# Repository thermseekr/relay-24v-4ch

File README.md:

# RELAY-24V-4CH

Relay board with 4x 24 VDC relays. This board is designed to be used togheter with [ESP-24V-16CH](https://github.com/thermseekr/esp-24v-16ch) and [ESP-24V-32CH](https://github.com/thermseekr/esp-24v-32ch), but can be driven by any 24V control circuit compatible with NPN inputs.

The dimensions are such that the boards can be mounted on a PCB DIN rail holder from the Brazilian manufacturer Metaltex, check [here](https://www.metaltex.com.br/produtos/componentes/suportes/sp7-suporte-para-montagem-de-placa-de-circuito-impresso-em-trilho-din) for details.

Board V1 uses Omron 16A relays and is limited to 12A/channel, board V2 uses Omron 10A relays and is limited to 8A/channel. The current limits are imposed per copper trace capacity.

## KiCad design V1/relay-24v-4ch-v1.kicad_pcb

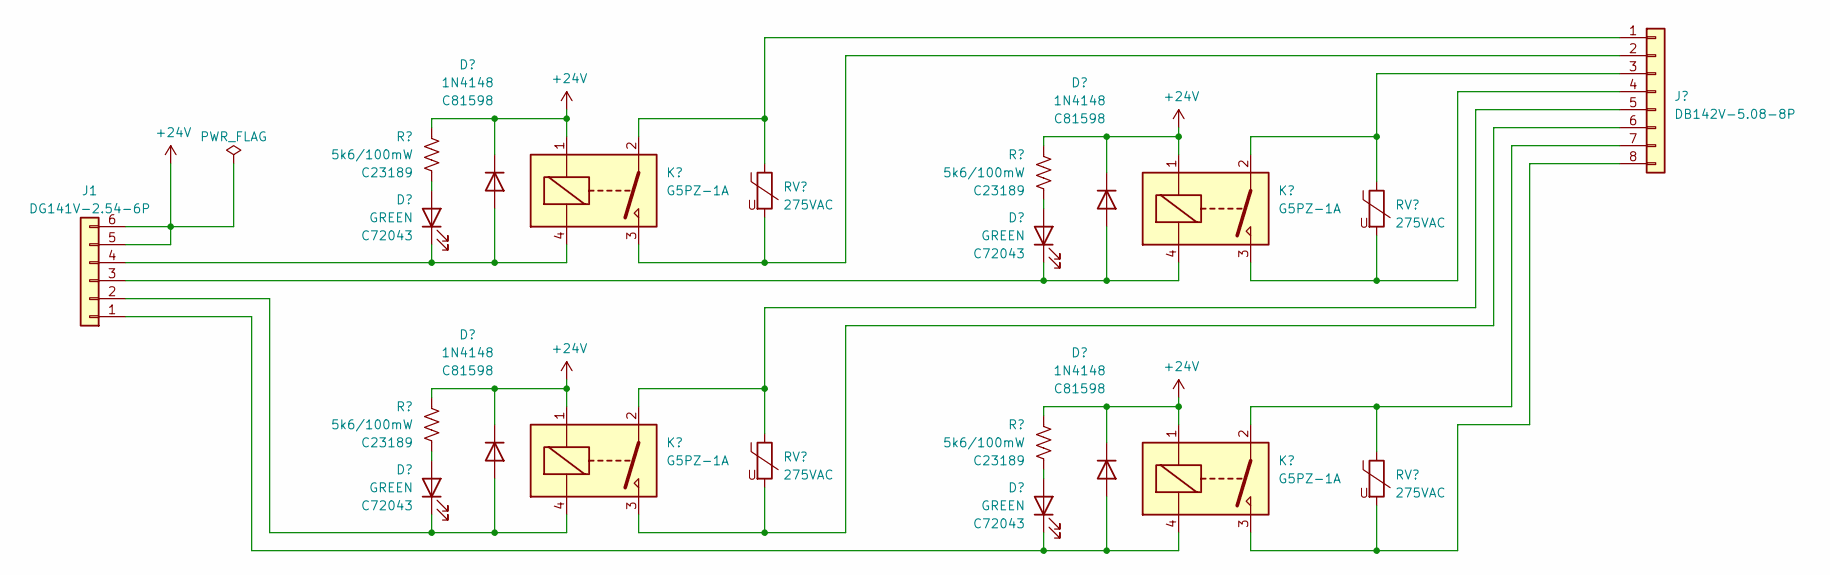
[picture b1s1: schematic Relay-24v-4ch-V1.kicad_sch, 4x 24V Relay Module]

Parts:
D1, D3, D5, D7: GREEN; LED_0603_1608Metric; Mfr PN 19-217/GHC-YR1S2/3T; LCSC Part # C72043
D2, D4, D6, D8: 1N4148; D_SOD-123; Mfr PN 1N4148W; LCSC Part # C81598
J1: DG141V-2.54-6P; TerminalBlock_Dibo_DB141V-2.54-6P_1x06_P2.54mm_Vertical; Mfr PN DB141V-2.54-5P; JLCPCB BOM 1
J2: DB142V-5.08-8P; TerminalBlock_Dibo_DB142V-5.08-8P_1x08_P5.08mm_Vertical; Mfr PN DB142V-5.08-8P; JLCPCB BOM 1
K1, K2, K3, K4: G5PZ-1A; Relay_SPST_Omron_G5PZ-1A; Mfr PN G5PZ-1A; JLCPCB BOM 0
R1, R2, R3, R4: 5k6/100mW; R_0603_1608Metric; Mfr PN 0805W8F4701T5E; LCSC Part # C23189
RV1, RV2, RV3, RV4: 275VAC; RV_Disc_D9.50mm_W3.6mm_P5.08mm; Mfr PN RM07D431KC1IE100; JLCPCB BOM 1

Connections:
+24V: D2.1 (K), D4.1 (K), D6.1 (K), D8.1 (K), J1.5, J1.6, K1.1, K2.1, K3.1, K4.1, R1.1, R2.1, R3.1, R4.1
unnamed: D1.2 (A), R1.2
unnamed: D1.1 (K), D2.2 (A), J1.4, K1.4
unnamed: D3.2 (A), R2.2
unnamed: D3.1 (K), D4.2 (A), J1.3, K2.4
unnamed: D5.2 (A), R3.2
unnamed: D5.1 (K), D6.2 (A), J1.2, K3.4
unnamed: D7.2 (A), R4.2
unnamed: D7.1 (K), D8.2 (A), J1.1, K4.4
unnamed: J2.1, K1.2, RV1.1
unnamed: J2.2, K1.3, RV1.2
unnamed: J2.3, K2.2, RV2.1
unnamed: J2.4, K2.3, RV2.2
unnamed: J2.5, K3.2, RV3.1
unnamed: J2.6, K3.3, RV3.2
unnamed: J2.7, K4.2, RV4.1
unnamed: J2.8, K4.3, RV4.2

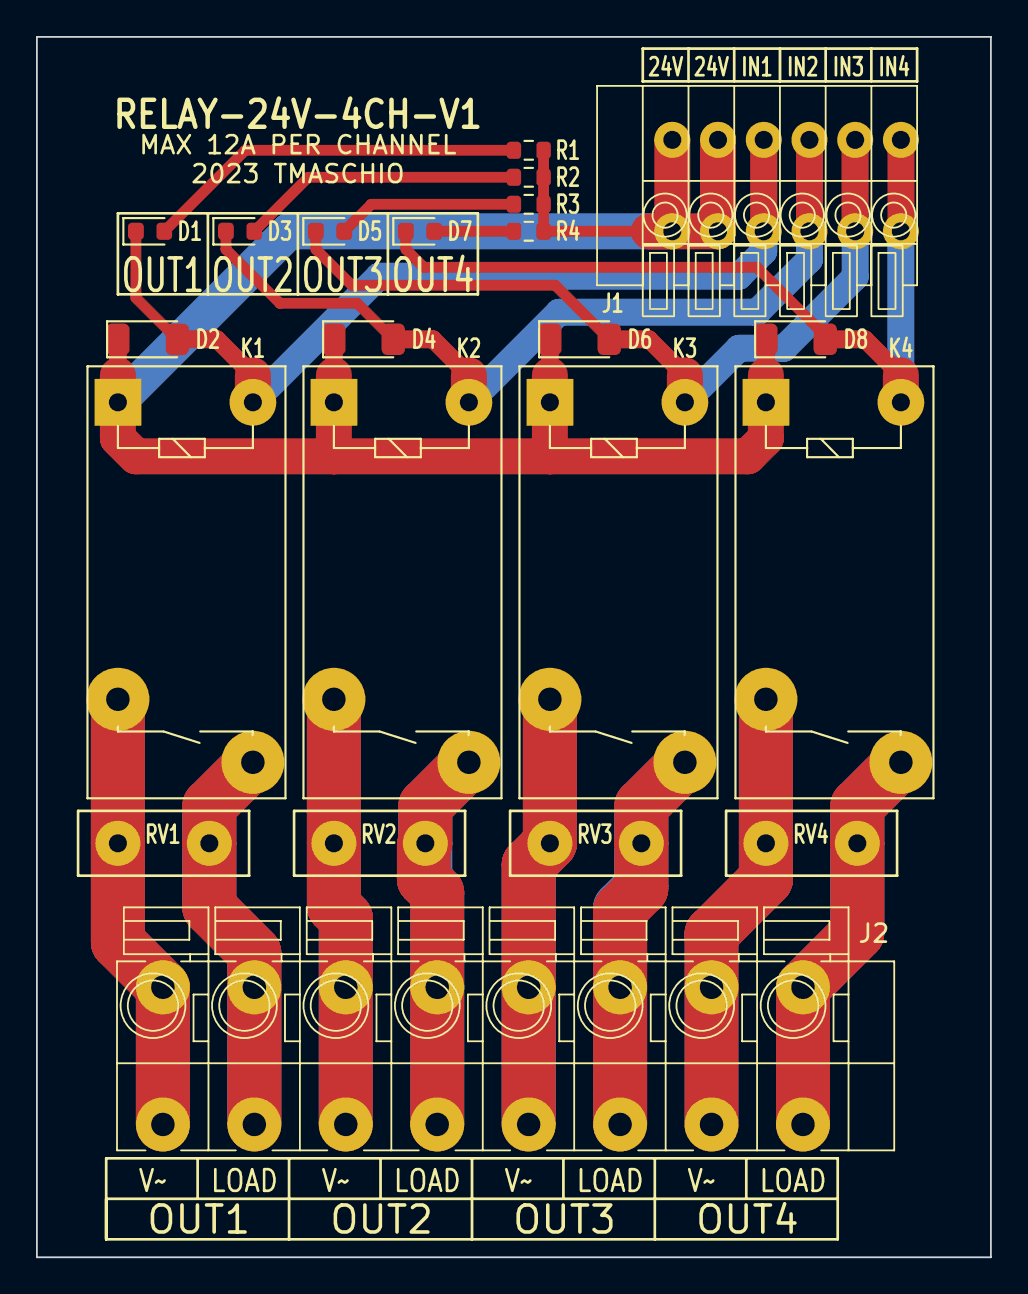
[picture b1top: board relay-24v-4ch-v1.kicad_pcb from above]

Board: 2 copper layers, 53.0 x 67.8 mm, 22 parts (0 on the bottom side), 17 nets.

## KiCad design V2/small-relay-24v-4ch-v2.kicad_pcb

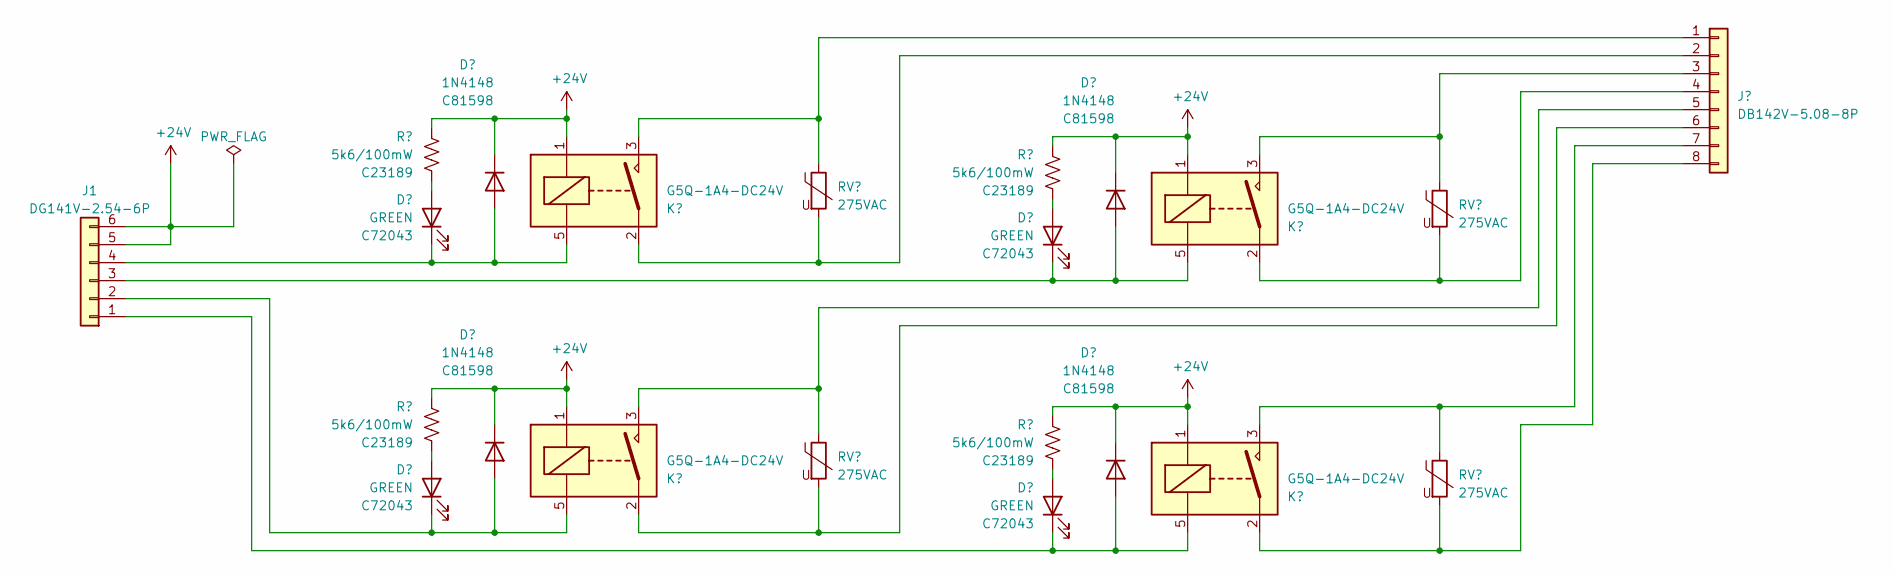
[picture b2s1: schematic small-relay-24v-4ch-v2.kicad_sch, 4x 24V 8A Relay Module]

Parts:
D1, D3, D5, D7: GREEN; LED_0603_1608Metric; Mfr PN 19-217/GHC-YR1S2/3T; LCSC Part # C72043
D2, D4, D6, D8: 1N4148; D_SOD-123; Mfr PN 1N4148W; LCSC Part # C81598
J1: DG141V-2.54-6P; TerminalBlock_Dibo_DB141V-2.54-6P_1x06_P2.54mm_Vertical; Mfr PN DB141V-2.54-5P; JLCPCB BOM 1
J2: DB142V-5.08-8P; TerminalBlock_Dibo_DB142V-5.08-8P_1x08_P5.08mm_Vertical; Mfr PN DB142V-5.08-8P; JLCPCB BOM 1
K1, K2, K3, K4: G5Q-1A4-DC24V; Relay_SPST_Omron-G5Q-1A; Mfr PN G5Q-1A4-DC24V; JLCPCB BOM 1
R1, R2, R3, R4: 5k6/100mW; R_0603_1608Metric; Mfr PN 0805W8F4701T5E; LCSC Part # C23189
RV1, RV2, RV3, RV4: 275VAC; RV_Disc_D9.50mm_W3.6mm_P5.08mm; Mfr PN RM07D431KC1IE100; JLCPCB BOM 1

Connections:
+24V: D2.1 (K), D4.1 (K), D6.1 (K), D8.1 (K), J1.5, J1.6, K1.1, K2.1, K3.1, K4.1, R1.1, R2.1, R3.1, R4.1
unnamed: D1.2 (A), R1.2
unnamed: D1.1 (K), D2.2 (A), J1.4, K1.5
unnamed: D3.2 (A), R2.2
unnamed: D3.1 (K), D4.2 (A), J1.3, K2.5
unnamed: D5.2 (A), R3.2
unnamed: D5.1 (K), D6.2 (A), J1.2, K3.5
unnamed: D7.2 (A), R4.2
unnamed: D7.1 (K), D8.2 (A), J1.1, K4.5
unnamed: J2.1, K1.3, RV1.1
unnamed: J2.2, K1.2, RV1.2
unnamed: J2.3, K2.3, RV2.1
unnamed: J2.4, K2.2, RV2.2
unnamed: J2.5, K3.3, RV3.1
unnamed: J2.6, K3.2, RV3.2
unnamed: J2.7, K4.3, RV4.1
unnamed: J2.8, K4.2, RV4.2

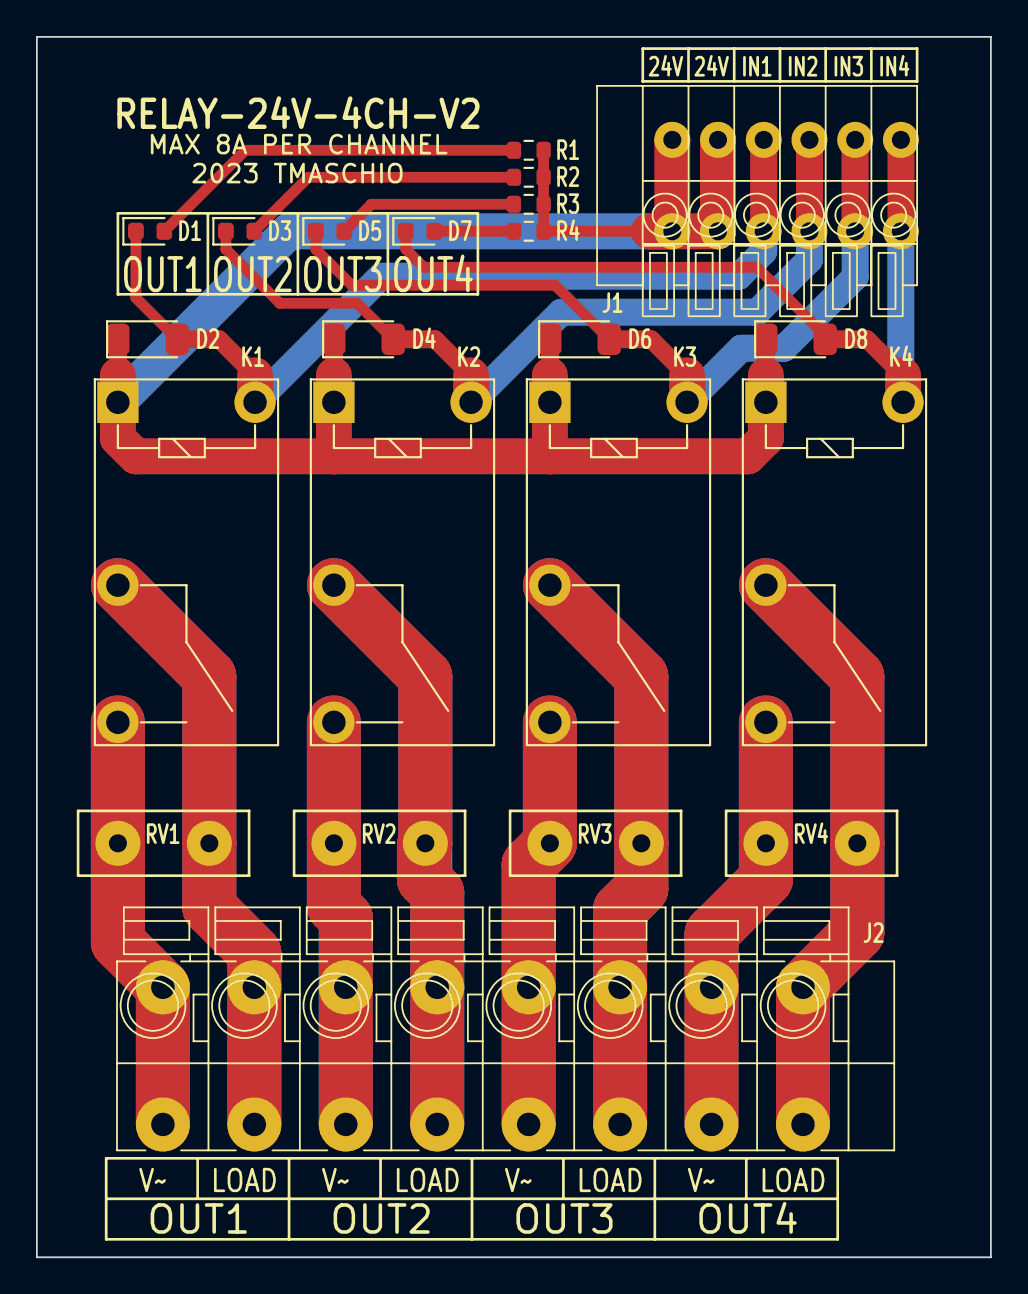
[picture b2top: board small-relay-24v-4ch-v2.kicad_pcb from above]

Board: 2 copper layers, 53.0 x 67.8 mm, 22 parts (0 on the bottom side), 17 nets.

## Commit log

2023-05-22 Update board images
2023-05-22 Updates for fabrication
2023-05-23 Adjustments for fabrication
2023-06-26 Add V2 board with Songle relays.
2023-08-20 Input connector rotated 180deg
2023-08-21 Repository reorg and cleanup
2023-08-31 Varistor updated
2023-09-02 Design optimization
2023-09-04 Redone everything
2023-09-04 Standarization
2023-09-04 Minor updates
2023-09-04 New board image
2023-09-06 Rename to lowercase
2024-10-02 Update to Kicad 8
